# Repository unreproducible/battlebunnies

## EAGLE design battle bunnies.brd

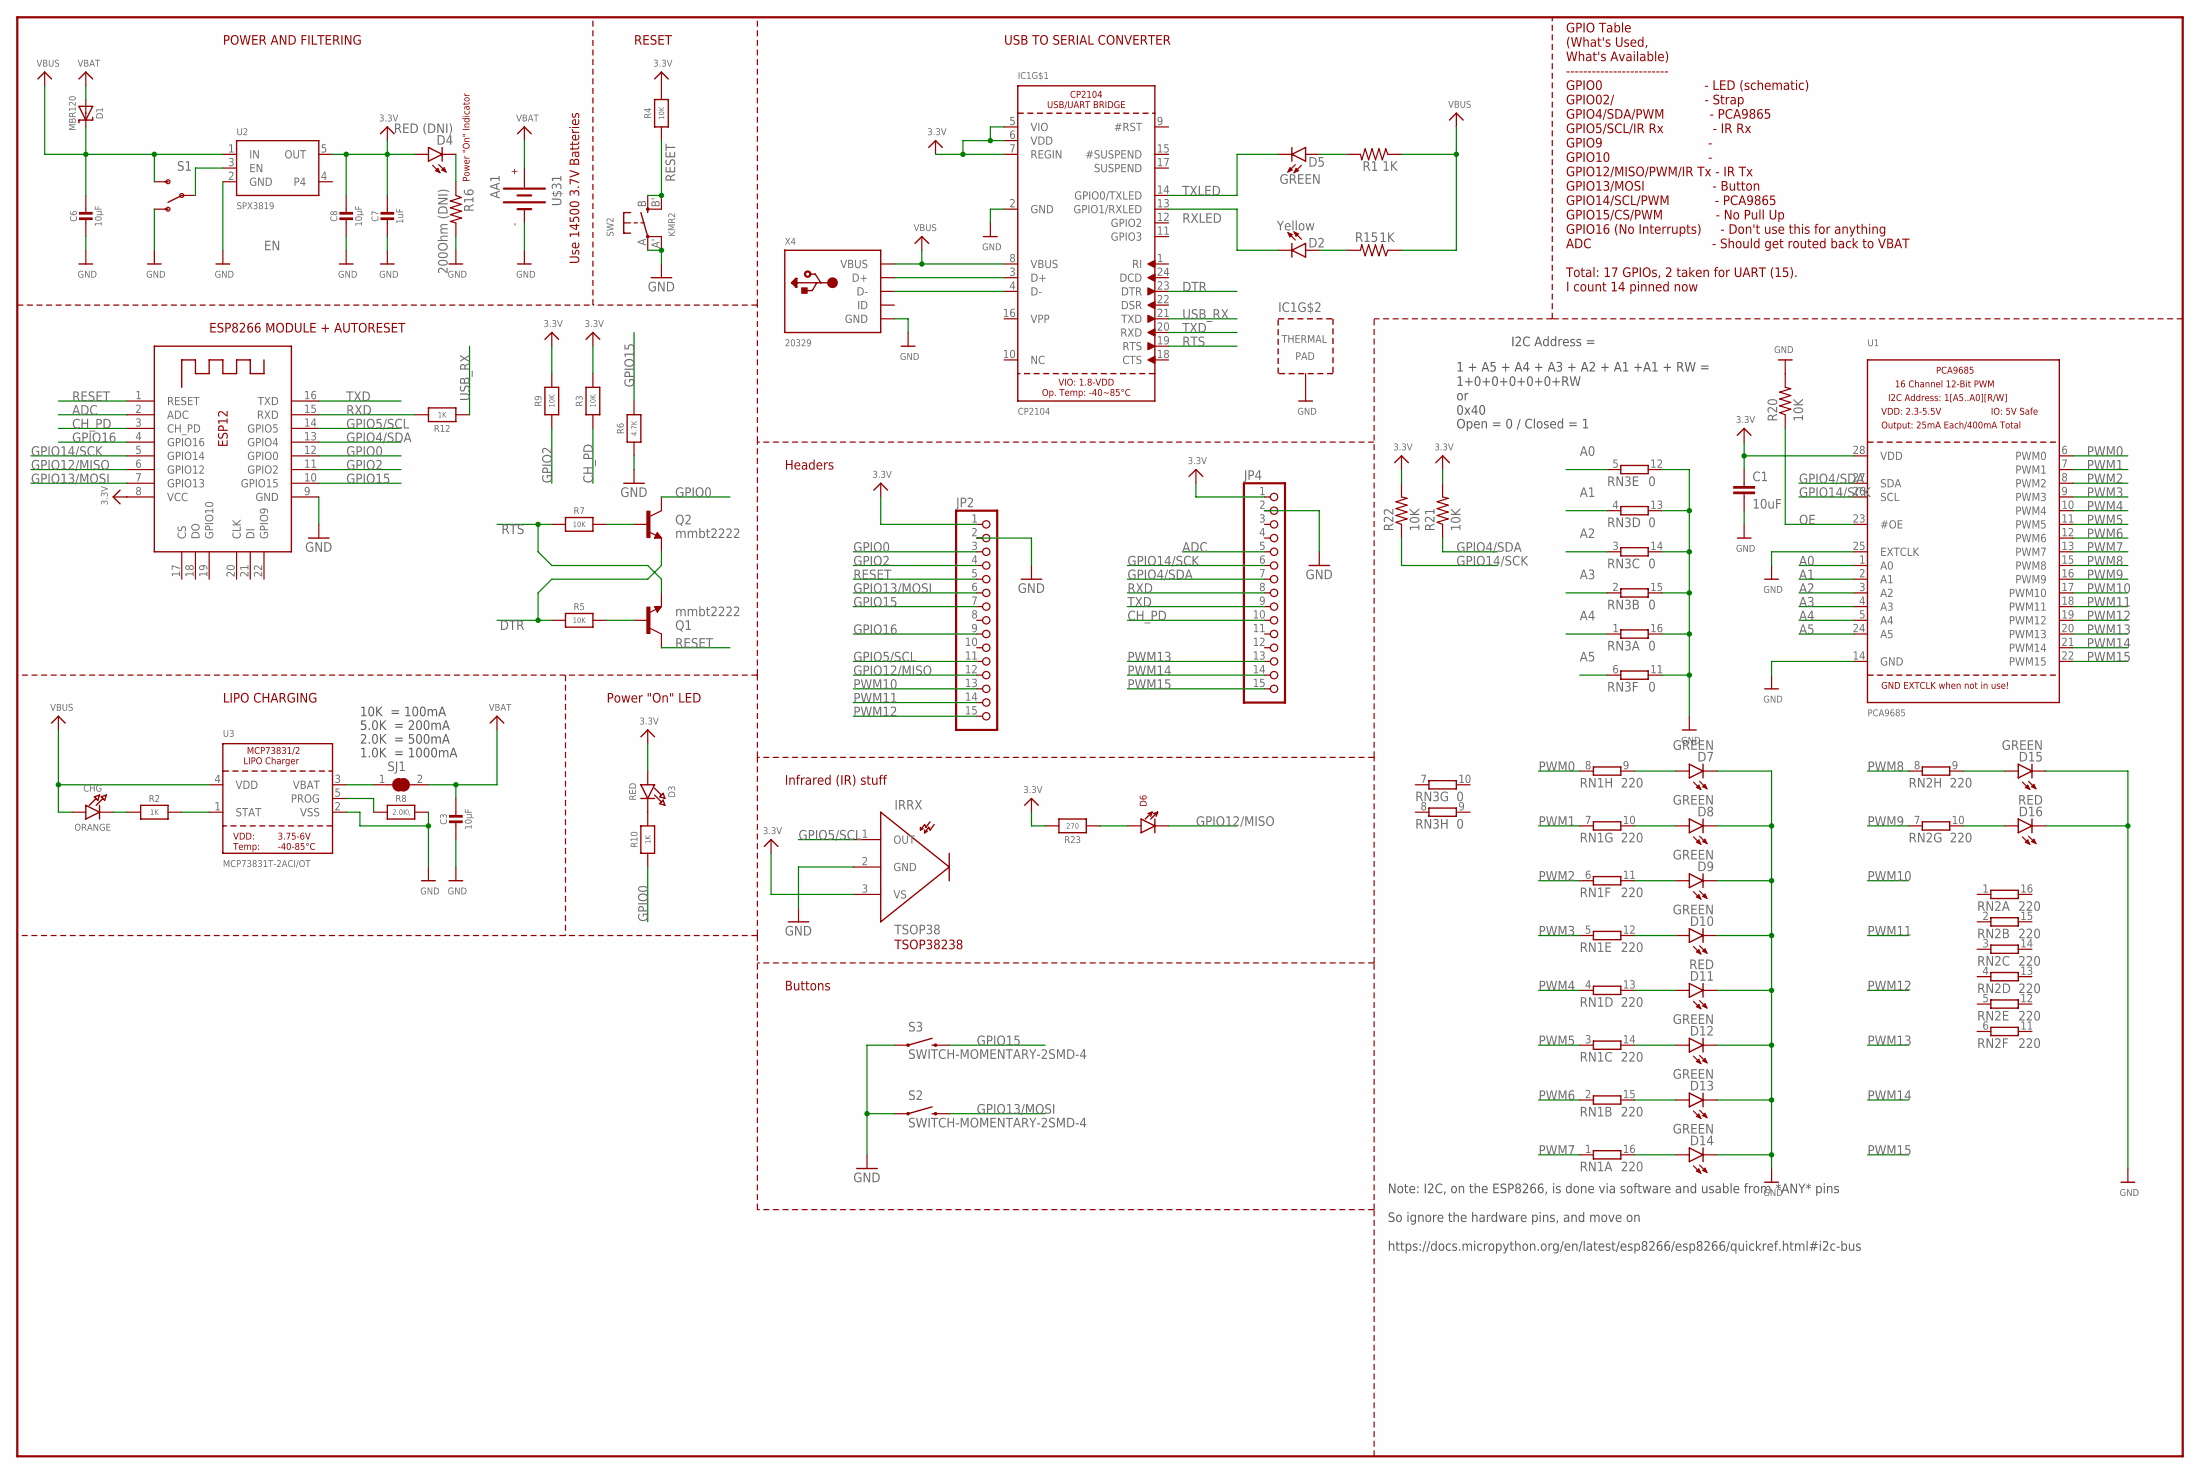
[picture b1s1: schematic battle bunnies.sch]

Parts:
C1: 10uF; 0805-CAP
C3, C6, C8: 10µF; 0805-NO
C7: 1uF; 0603-NO
CHG: ORANGE; CHIPLED_0805_NOOUTLINE
D1: MBR120; SOD-123
D2: Yellow; LED-0603
D3: RED; CHIPLED_0805_NOOUTLINE
D4: RED (DNI); LED-0603
D5, D7, D8, D9, D10, D12, D13, D14, D15: GREEN; LED-0603
D6: LTE-302
D11, D16: RED; LED-0603
IC1: CP2104; QFN24_4MM_SMSC
IRRX: TSOP38
JP2, JP4: PINHD-1X15; 1X15
Q1, Q2: mmbt2222; SOT23-3
R1, R15: 1K; 0603-RES
R2, R10: 1K; 0603-NO
R3, R4, R5, R9: 10K; 0603-NO
R6: 4.7K; 0603-NO
R7: 10K; _0603MP
R8: 2.0K\; 0603-NO
R12: 1K; _0603MP
R16: 200Ohm (DNI); 0603-RES
R20, R21, R22: 10K; 0805
R23: 270; 0603-NO
RN1, RN2: 220; EXB2HV
RN3: 0; EXB2HV
S1: SWITCH-SPDT-SMD-A; SWITCH-SPST-SMD-A
S2, S3: SWITCH-MOMENTARY-2SMD-4; TACTILE_SWITCH_TALL
SJ1: SOLDERJUMPER_CLOSED; SOLDERJUMPER_CLOSEDWIRE@1
SW2: KMR2; BTN_KMR2_4.6X2.8
U1: PCA9685; TSSOP28
U2: SPX3819; SOT23-5
U3: MCP73831T-2ACI/OT; SOT23-5
U$31: AA1
X2: ESP-12; ESP-12E
X4: 20329; MICRO-USB5+6P-SMD-0.65-B

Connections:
3.3V: C1.1, C7.1, C8.1, D3.A, D4.A, IC1.5 (VIO), IC1.6 (VDD), IC1.7 (REGIN), IRRX.3 (VS), JP2.1, JP4.1, R1.1, R3.2, R4.2, R9.2, R15.1, R21.2, R22.2, R23.2, U1.28 (VDD), U2.5 (OUT), X2.8 (VCC)
A0: RN3.5 (1), U1.1 (A0)
A1: RN3.4 (1), U1.2 (A1)
A2: RN3.3 (1), U1.3 (A2)
A3: RN3.2 (1), U1.4 (A3)
A4: RN3.1, U1.5 (A4)
A5: RN3.6 (1), U1.24 (A5)
ADC: JP4.5, X2.2 (ADC)
CH_PD: JP4.10, R3.1, X2.3 (CH_PD)
DTR: IC1.23 (DTR), Q2.2 (E), R5.1
EN: S1.2, U2.3 (EN)
GND: C1.2, C3.2, C6.2, C7.2, C8.2, D7.C, D8.C, D9.C, D10.C, D11.C, D12.C, D13.C, D14.C, D15.C, D16.C, IC1.2 (GND), IC1.THERM (TP), IRRX.2 (GND), JP2.2, JP4.2, R6.1, R8.2, R16.2, R20.2, RN3.11 (2), RN3.12 (2), RN3.13 (2), RN3.14 (2), RN3.15 (2), RN3.16 (2), S1.1 (O), S2.A2 (1), S3.A2 (1), SW2.A, SW2.A' (P1), U1.14 (GND), U1.25 (EXTCLK), U2.2 (GND), U3.2 (VSS), U$31.NEG (-), X2.9 (GND), X4.5 (GND), X4.S1 (GND), X4.S2 (GND), X4.S3 (GND), X4.S4 (GND), X4.S5 (GND), X4.S6 (GND)
GPIO0: JP2.3, Q2.3 (C), R10.1, X2.12 (GPIO0)
GPIO2: JP2.4, R9.1, X2.11 (GPIO2)
GPIO4/SDA: JP4.7, R21.1, U1.27 (SDA), X2.13 (GPIO4)
GPIO5/SCL: IRRX.1 (OUT), JP2.11, X2.14 (GPIO5)
GPIO12/MISO: D6.C, JP2.12, X2.6 (GPIO12)
GPIO13/MOSI: JP2.6, S2.B2 (2), X2.7 (GPIO13)
GPIO14/SCK: JP4.6, R22.1, U1.26 (SCL), X2.5 (GPIO14)
GPIO15: JP2.7, R6.2, S3.B2 (2), X2.10 (GPIO15)
GPIO16: JP2.9, X2.4 (GPIO16)
unnamed: CHG.C, R2.1
unnamed: R8.1, U3.5 (PROG)
unnamed: R2.2, U3.1 (STAT)
unnamed: D4.C, R16.1
unnamed: D3.C, R10.2
unnamed: D5.A, R1.2
unnamed: SJ1.1, U3.3 (VBAT)
unnamed: D2.A, R15.2
unnamed: Q1.1 (B), R5.2
unnamed: Q2.1 (B), R7.2
unnamed: D6.A, R23.1
unnamed: D13.A, RN1.15 (2)
unnamed: D14.A, RN1.16 (2)
unnamed: D12.A, RN1.14 (2)
unnamed: D11.A, RN1.13 (2)
unnamed: D10.A, RN1.12 (2)
unnamed: D9.A, RN1.11 (2)
unnamed: D8.A, RN1.10 (2)
unnamed: D7.A, RN1.9 (2)
unnamed: D15.A, RN2.9 (2)
unnamed: D16.A, RN2.10 (2)
OE: R20.1, U1.23 (#OE)
PWM0: RN1.8 (1), U1.6 (PWM0)
PWM1: RN1.7 (1), U1.7 (PWM1)
PWM2: RN1.6 (1), U1.8 (PWM2)
PWM3: RN1.5 (1), U1.9 (PWM3)
PWM4: RN1.4 (1), U1.10 (PWM4)
PWM5: RN1.3 (1), U1.11 (PWM5)
PWM6: RN1.2 (1), U1.12 (PWM6)
PWM7: RN1.1, U1.13 (PWM7)
PWM8: RN2.8 (1), U1.15 (PWM8)
PWM9: RN2.7 (1), U1.16 (PWM9)
PWM10: JP2.13, U1.17 (PWM10)
PWM11: JP2.14, U1.18 (PWM11)
PWM12: JP2.15, U1.19 (PWM12)
PWM13: JP4.13, U1.20 (PWM13)
PWM14: JP4.14, U1.21 (PWM14)
PWM15: JP4.15, U1.22 (PWM15)
RESET: JP2.5, Q1.3 (C), R4.1, SW2.B (S), SW2.B' (S1), X2.1 (RESET)
RTS: IC1.19 (RTS), Q1.2 (E), R7.1
RXD: JP4.8, R12.2, X2.15 (RXD)
RXLED: D2.C, IC1.13 (GPIO1/RXLED)
TXD: IC1.20 (RXD), JP4.9, X2.16 (TXD)
TXLED: D5.C, IC1.14 (GPIO0/TXLED)
USBD_N: IC1.4 (D-), X4.2 (D-)
USBD_P: IC1.3 (D+), X4.3 (D+)
USB_RX: IC1.21 (TXD), R12.1
VBAT: C3.1, D1.A, SJ1.2, U$31.POS (+)
VBUS: C6.1, CHG.A, D1.C, IC1.8 (VBUS), S1.3 (S), U2.1 (IN), U3.4 (VDD), X4.1 (VBUS)

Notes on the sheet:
POWER AND FILTERING
RESET
10K = 100mA
5.0K = 200mA
2.0K = 500mA
1.0K = 1000mA
USB TO SERIAL CONVERTER
LIPO CHARGING
Power "On" LED
ESP8266 MODULE + AUTORESET
Power "On" Indicator
GPIO Table (What's Used, What's Available) ------------------------ GPIO0 - LED (schematic) GPIO02/ - Strap GPIO4/SDA/PWM - PCA9865 GPIO5/SCL/IR Rx - IR Rx GPIO9 - GPIO10 - GPIO12/MISO/PWM/IR Tx - IR Tx GPIO13/MOSI - Button GPIO14/SCL/PWM - PCA9865 GPIO15/CS/PWM - No Pull Up GPIO16 (No Interrupts) 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
1 + A5 + A4 + A3 + A2 + A1 +A1 + RW = 1+0+0+0+0+0+RW or 0x40
I2C Address =
Open = 0 / Closed = 1
Note: I2C, on the ESP8266, is done via software and usable from *ANY* pins So ignore the hardware pins, and move on https://docs.micropython.org/en/latest/esp8266/esp8266/quickref.html#i2c-bus
Headers
Infrared (IR) stuff
TSOP38238
Buttons
Use 14500 3.7V Batteries

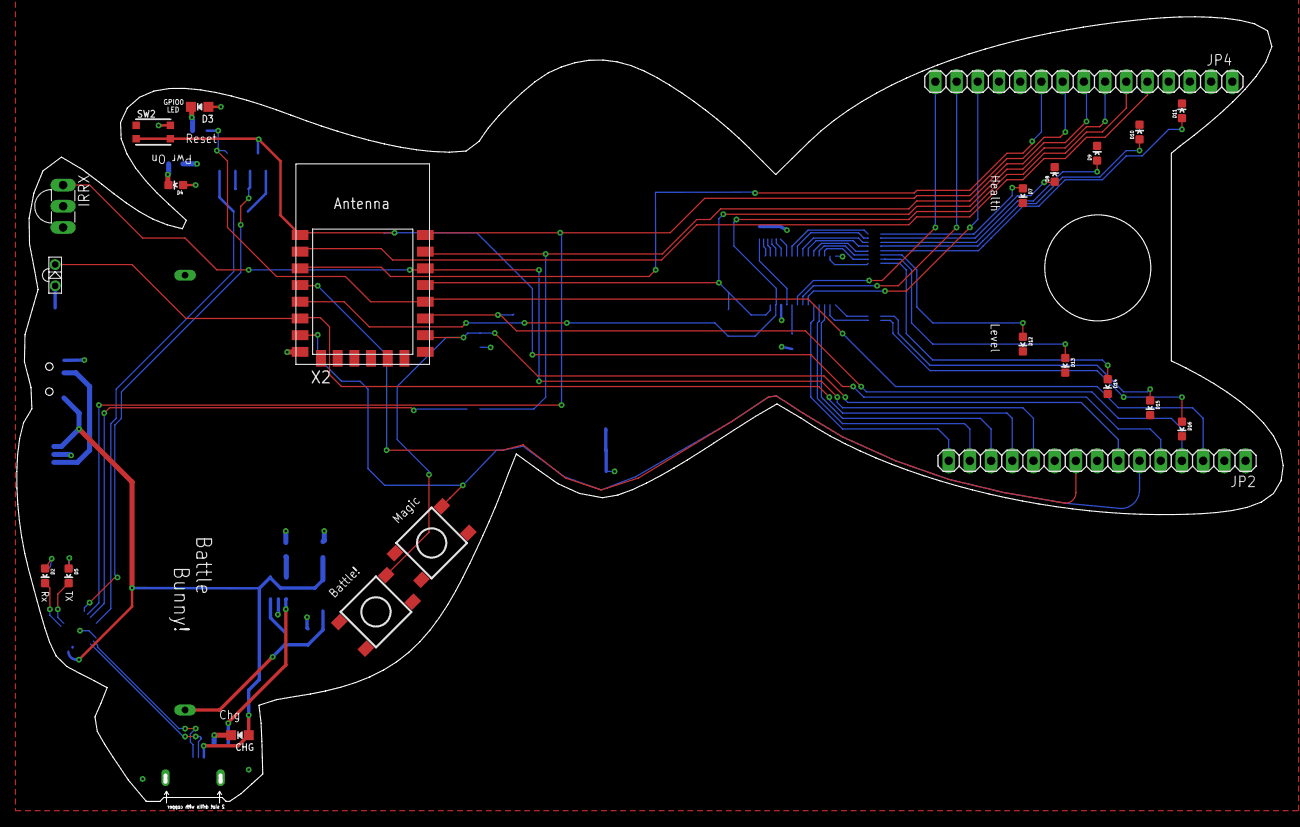
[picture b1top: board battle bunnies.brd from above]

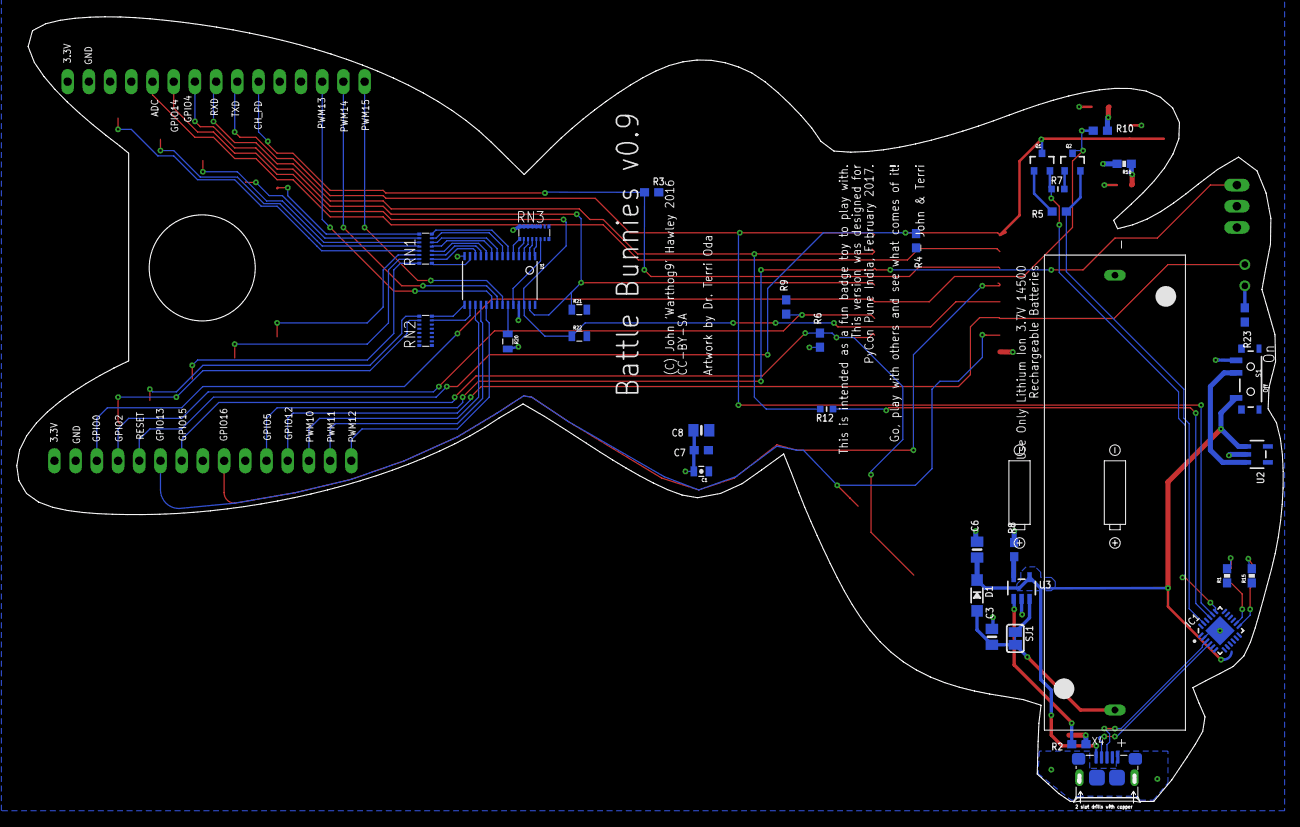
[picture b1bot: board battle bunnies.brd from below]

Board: 2 copper layers, 151.7 x 94.0 mm, 59 parts (36 on the bottom side), 70 nets.

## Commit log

2017-01-02 Adding Board Schematic, Layout, & additional files for design
2017-01-02 Re-working for amica module
2018-04-06 USB: Swapping the USB part out - twas unobtanium
    The 4UCONN connector that Adafruit used is basically made of unobtanium
    and more or less doesn't exist. The part that was trying to be used
    the rear prongs did not match up by any stretch of the imagination.
    A mess of e-mails an annoyance ensued.
    I'm swapping out the part on everything I can now, this seems to be
    more common, and there's parts that are similar enough to it that

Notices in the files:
battle bunnies.brd:
CC-BY-SA
parts and their libraries:
SparkFun-Capacitors: Licensing: Creative Commons ShareAlike 4.0 International - https://creativecommons.org/licenses/by-sa/4.0
microbuilder: This work is placed in the public domain, and may be freely used for commercial and non-commercial work with the following conditions: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
